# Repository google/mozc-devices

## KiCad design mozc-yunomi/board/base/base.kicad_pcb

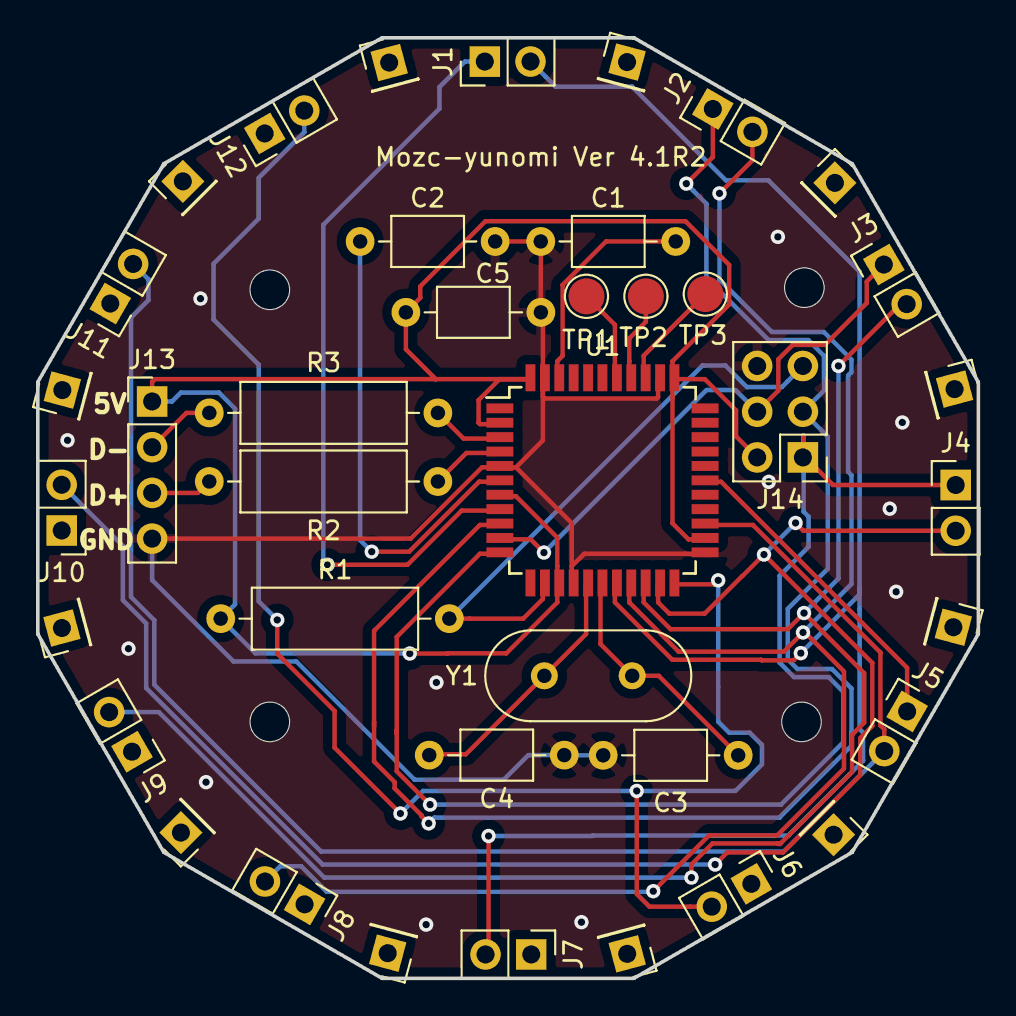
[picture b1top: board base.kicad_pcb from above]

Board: 2 copper layers, 52.2 x 52.2 mm, 39 parts (0 on the bottom side), 25 nets.

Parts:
C1: 0.1uF; C_Axial_L3.8mm_D2.6mm_P7.50mm_Horizontal
C2: 1uF; C_Axial_L3.8mm_D2.6mm_P7.50mm_Horizontal
C3, C4, C5: C; C_Axial_L3.8mm_D2.6mm_P7.50mm_Horizontal
J1, J2, J3, J4, J5, J6, J7, J8, J9, J10, J11, J12: Conn_01x02_Male; PinHeader_1x02_P2.54mm_Vertical
J13: Conn_01x04_Male; PinHeader_1x04_P2.54mm_Vertical
J14: Conn_02x03_Odd_Even; PinHeader_2x03_P2.54mm_Vertical
J15, J16, J17, J18, J19, J20, J21, J22, J23, J24, J25, J26: Conn_01x01_Male; PinHeader_1x01_P2.54mm_Vertical
R1: 10K; R_Axial_DIN0309_L9.0mm_D3.2mm_P12.70mm_Horizontal
R2, R3: 22; R_Axial_DIN0309_L9.0mm_D3.2mm_P12.70mm_Horizontal
TP1, TP2, TP3: TestPoint; TestPoint_Pad_D2.0mm
U1: ATmega32U4-AU; TQFP-44_10x10mm_P0.8mm
Y1: 16MHz; Crystal_HC49-4H_Vertical

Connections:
+5V: C5.1, J13.1, J14.2, R1.1, U1.2, U1.7, U1.14, U1.24, U1.34, U1.44
COL0: J1.2, J7.2, U1.18
COL1: J2.2, J8.2, U1.19
COL2: J3.2, J9.2, U1.20
COL3: J4.2, J10.2, U1.21
COL4: J5.2, J11.2, U1.25
COL5: J6.2, J12.2, U1.22
D+: J13.3, R2.2
D-: J13.2, R3.2
GND: C1.1, C2.2, C3.1, C4.1, C5.2, J13.4, J14.6, U1.5, U1.15, U1.23, U1.35, U1.43
MISO: J4.1, J14.1, U1.11
MOSI: J3.1, J14.4, U1.10
unnamed: C1.2, U1.42
unnamed: C2.1, U1.6
unnamed: R2.1, U1.4
unnamed: R3.1, U1.3
unnamed: TP1.1, U1.38
unnamed: TP2.1, U1.37
unnamed: TP3.1, U1.36
ROW0: J1.1, U1.8
ROW1: J2.1, J14.3, U1.9
ROW4: J5.1, U1.28
RST: J14.5, R1.2, U1.13
XTAL1: C3.2, U1.17, Y1.1
XTAL2: C4.2, U1.16, Y1.2

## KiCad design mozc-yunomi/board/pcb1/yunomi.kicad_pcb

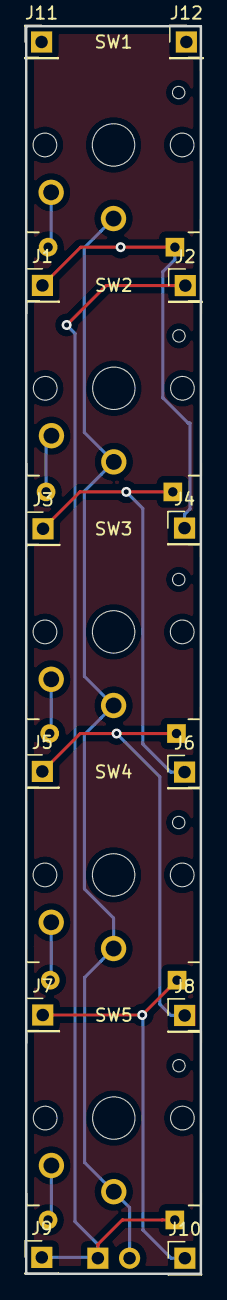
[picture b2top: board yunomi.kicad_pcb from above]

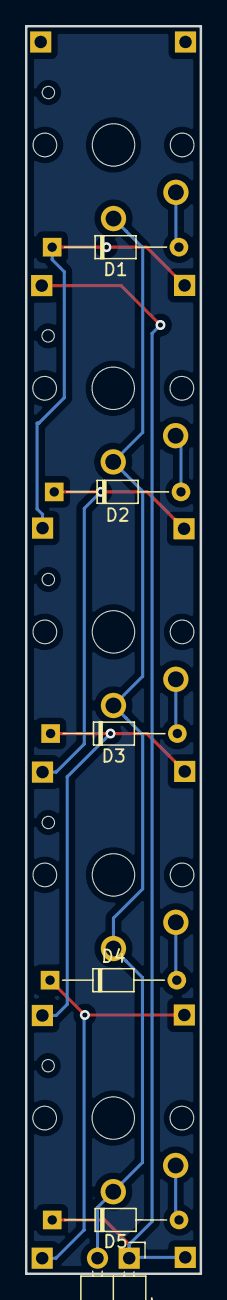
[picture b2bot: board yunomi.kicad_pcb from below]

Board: 2 copper layers, 14.0 x 100.0 mm, 23 parts (6 on the bottom side), 11 nets.

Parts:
D1, D2, D3, D4, D5: D; D_DO-34_SOD68_P10.16mm_Horizontal
J1, J2, J3, J4, J5, J6, J7, J8, J9, J10, J11, J12: Conn_01x01_Male; PinHeader_1x01_P2.54mm_Vertical
J13: Conn_01x02_Male; PinHeader_1x02_P2.54mm_Horizontal
SW1, SW2, SW3, SW4, SW5: SW_Push; SW_PG1350

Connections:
unnamed: D1.1, J1.1, J4.1
unnamed: D1.2, SW1.2
unnamed: D2.1, J3.1, J6.1
unnamed: D2.2, SW2.2
unnamed: D3.1, J5.1, J8.1
unnamed: D3.2, SW3.2
unnamed: D4.1, J7.1, J10.1
unnamed: D4.2, SW4.2
unnamed: D5.1, J2.1, J9.1, J13.1
unnamed: D5.2, SW5.2
unnamed: J13.2, SW1.1, SW2.1, SW3.1, SW4.1, SW5.1
